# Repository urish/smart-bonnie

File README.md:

Install the following:

* [Arduino nRF5](https://github.com/sandeepmistry/arduino-nRF5)
* [BLEPeripheral Library](https://github.com/sandeepmistry/arduino-BLEPeripheral)

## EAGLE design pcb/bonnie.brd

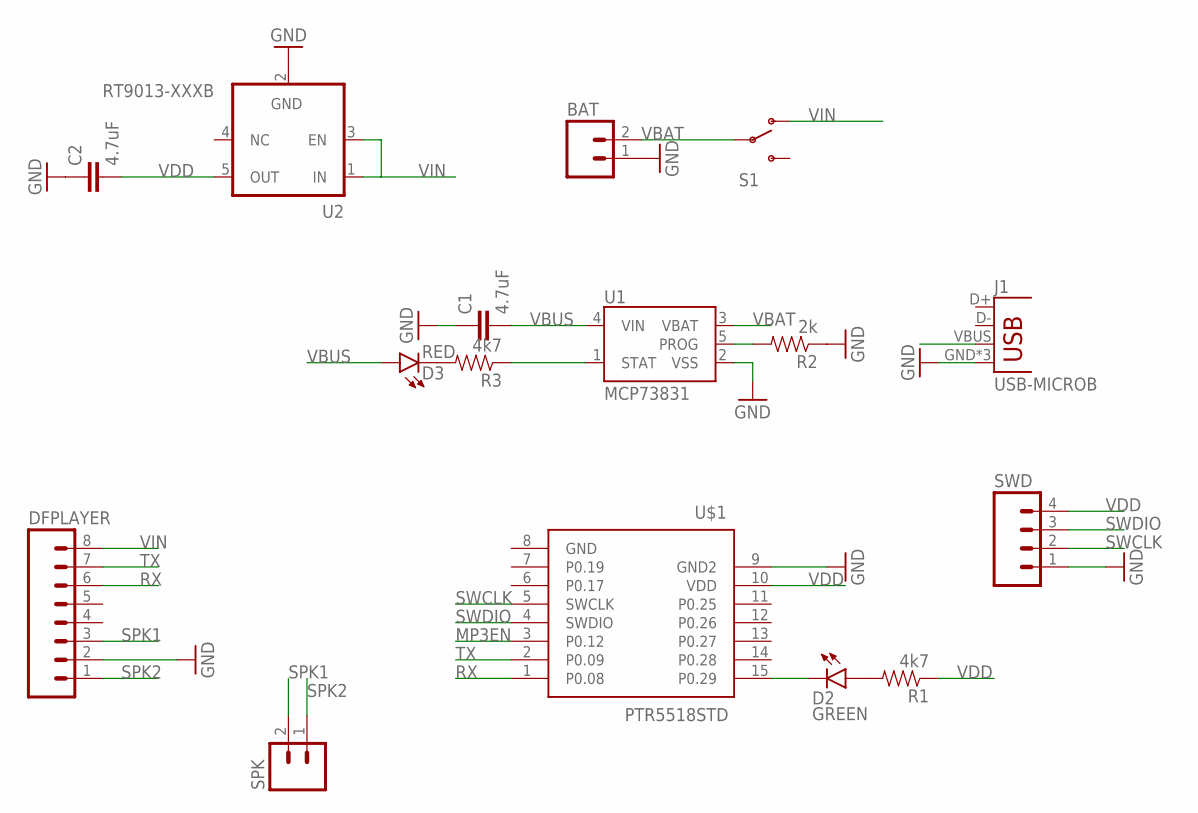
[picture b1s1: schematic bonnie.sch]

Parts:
BAT: M02JST-PTH-2; JST-2-PTH
C1, C2: 4.7uF; 0603-CAP
D2: GREEN; LED-0603
D3: RED; LED-0603
DFPLAYER: M08LOCK; 1X08_LOCK
J1: USB-MICROB
R1, R3: 4k7; 0603-RES
R2: 2k; 0603-RES
S1: SWITCH-SPDTPTH; SWITCH-SPDT
SPK: M02JST-PTH-VERT; JST-2-PTH-VERT
SWD: M04LOCK; 1X04_LOCK
U1: MCP73831; SOT23-5
U2: RT9013-XXXB; SOT23-5
U$1: PTR5518STD; PTR5518

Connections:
GND: BAT.1, C1.1, C2.1, DFPLAYER.2, J1.GND, J1.MT1 (GND), J1.MT2 (GND), R2.1, SWD.1, U1.2 (VSS), U2.2 (GND), U$1.8 (GND), U$1.9 (GND2)
MP3EN: U$1.3 (P0.12)
unnamed: R2.2, U1.5 (PROG)
unnamed: D2.A, R1.2
unnamed: D2.C, U$1.15 (P0.29)
unnamed: R3.1, U1.1 (STAT)
unnamed: D3.C, R3.2
RX: DFPLAYER.6, U$1.1 (P0.08)
SPK1: DFPLAYER.3, SPK.2
SPK2: DFPLAYER.1, SPK.1
SWCLK: SWD.2, U$1.5 (SWCLK)
SWDIO: SWD.3, U$1.4 (SWDIO)
TX: DFPLAYER.7, U$1.2 (P0.09)
VBAT: BAT.2, S1.2, U1.3 (VBAT)
VBUS: C1.2, D3.A, J1.VBUS, U1.4 (VIN)
VDD: R1.1, SWD.4, U2.5 (OUT), U$1.10 (VDD)
VIN: DFPLAYER.8, S1.1 (O), U2.1 (IN), U2.3 (EN)

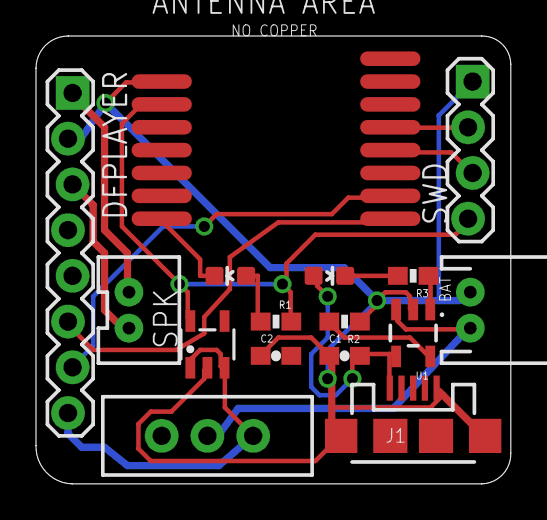
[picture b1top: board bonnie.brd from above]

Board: 2 copper layers, 26.4 x 24.9 mm, 16 parts (0 on the bottom side), 16 nets.

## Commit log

2016-12-16 Initial commit - say hi!
2016-12-17 travis configuration
2016-12-24 nrf51822 firmware
2016-12-24 Web interface to control bonnie
2016-12-24 add 3d model of bonnie
2016-12-26 add PCB design
2016-12-26 Firmware support for RAW commands
2016-12-26 add default sound set
2017-01-02 add charging mechanism, replace diode with a regulator
2017-01-03 fix silk screen
2017-01-03 hide vias
2017-01-17 add status LED to firmware
2017-01-19 Scan for ng-beacons
    Play a sound whenever a see one nearby
2017-01-21 Fix numerous bugs in the BLE scanning code
2017-01-21 add happy "angular" sound (#5)
2017-02-01 fix(firmware): fix player command
    play files according to their name, not physical order on sd card
2017-02-13 fix: incorrect led oritentation
2017-02-14 fix: improve LED control code
2017-02-14 feat: add "Oh no panic" sound
2017-04-22 switch to smaller package for LEDs (1206 -> 0603)
2017-08-05 add espruino code
2017-08-05 update board for PTR5618 module

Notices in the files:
parts and their libraries:
SparkFun-Connectors: Licensing: Creative Commons ShareAlike 4.0 International - https://creativecommons.org/licenses/by-sa/4.0
